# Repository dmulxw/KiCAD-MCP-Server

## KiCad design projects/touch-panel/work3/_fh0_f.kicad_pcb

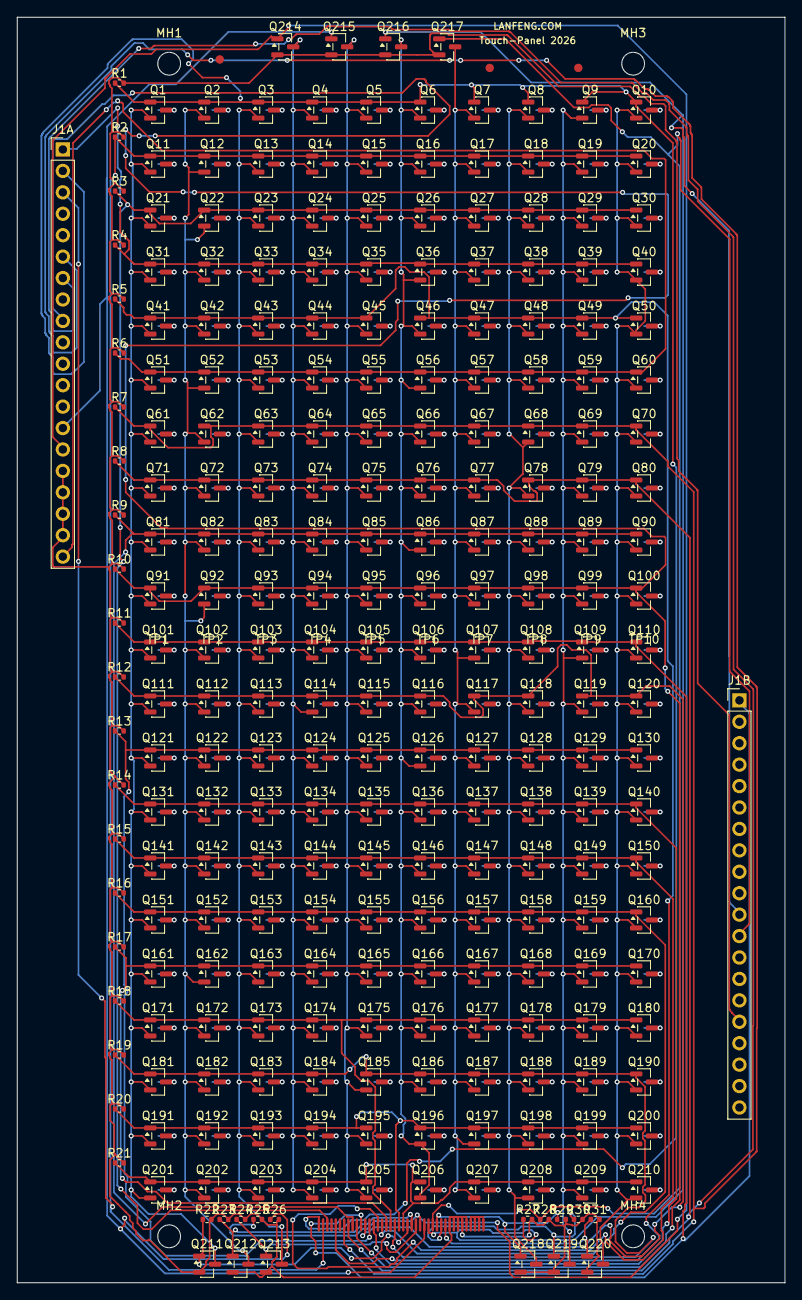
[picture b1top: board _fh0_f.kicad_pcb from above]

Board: 2 copper layers, 91.0 x 150.0 mm, 270 parts (0 on the bottom side), 253 nets.

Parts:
J1A, J1B: PinHeader_1x20_P2.54mm_Vertical
MH1, MH2, MH3, MH4: MountingHole_2.7mm
MK1, MK2, MK3: Fiducial_1mm_Mask2mm
Q1, Q2, Q3, Q4, Q5, Q6, Q7, Q8, Q9, Q10, Q11, Q12, Q13, Q14, Q15, Q16, Q17, Q18, Q19, Q20, Q21, Q22, Q23, Q24, Q25, Q26, Q27, Q28, Q29, Q30, Q31, Q32, Q33, Q34, Q35, Q36, Q37, Q38, Q39, Q40, Q41, Q42, Q43, Q44, Q45, Q46, Q47, Q48, Q49, Q50, Q51, Q52, Q53, Q54, Q55, Q56, Q57, Q58, Q59, Q60, Q61, Q62, Q63, Q64, Q65, Q66, Q67, Q68, Q69, Q70, Q71, Q72, Q73, Q74, Q75, Q76, Q77, Q78, Q79, Q80, Q81, Q82, Q83, Q84, Q85, Q86, Q87, Q88, Q89, Q90, Q91, Q92, Q93, Q94, Q95, Q96, Q97, Q98, Q99, Q100, Q101, Q102, Q103, Q104, Q105, Q106, Q107, Q108, Q109, Q110, Q111, Q112, Q113, Q114, Q115, Q116, Q117, Q118, Q119, Q120, Q121, Q122, Q123, Q124, Q125, Q126, Q127, Q128, Q129, Q130, Q131, Q132, Q133, Q134, Q135, Q136, Q137, Q138, Q139, Q140, Q141, Q142, Q143, Q144, Q145, Q146, Q147, Q148, Q149, Q150, Q151, Q152, Q153, Q154, Q155, Q156, Q157, Q158, Q159, Q160, Q161, Q162, Q163, Q164, Q165, Q166, Q167, Q168, Q169, Q170, Q171, Q172, Q173, Q174, Q175, Q176, Q177, Q178, Q179, Q180, Q181, Q182, Q183, Q184, Q185, Q186, Q187, Q188, Q189, Q190, Q191, Q192, Q193, Q194, Q195, Q196, Q197, Q198, Q199, Q200, Q201, Q202, Q203, Q204, Q205, Q206, Q207, Q208, Q209, Q210, Q211, Q212, Q213, Q214, Q215, Q216, Q217, Q218, Q219, Q220: AO3400; SOT-23
R1, R2, R3, R4, R5, R6, R7, R8, R9, R10, R11, R12, R13, R14, R15, R16, R17, R18, R19, R20, R21, R22, R23, R24, R25, R26, R27, R28, R29, R30, R31: 10k; R_0402_1005Metric
TP1, TP2, TP3, TP4, TP5, TP6, TP7, TP8, TP9, TP10: TouchPadColumn

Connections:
+3V3: J1B.17, J1B.18, J1B.19, J1B.20
COL0: Q1.2, Q11.2, Q21.2, Q31.2, Q41.2, Q51.2, Q61.2, Q71.2, Q81.2, Q91.2, Q101.2, Q111.2, Q121.2, Q131.2, Q141.2, Q151.2, Q161.2, Q171.2, Q181.2, Q191.2, Q201.2, Q211.3
COL1: Q2.2, Q12.2, Q22.2, Q32.2, Q42.2, Q52.2, Q62.2, Q72.2, Q82.2, Q92.2, Q102.2, Q112.2, Q122.2, Q132.2, Q142.2, Q152.2, Q162.2, Q172.2, Q182.2, Q192.2, Q202.2, Q212.3
COL2: Q3.2, Q13.2, Q23.2, Q33.2, Q43.2, Q53.2, Q63.2, Q73.2, Q83.2, Q93.2, Q103.2, Q113.2, Q123.2, Q133.2, Q143.2, Q153.2, Q163.2, Q173.2, Q183.2, Q193.2, Q203.2, Q213.3
COL3: Q4.2, Q14.2, Q24.2, Q34.2, Q44.2, Q54.2, Q64.2, Q74.2, Q84.2, Q94.2, Q104.2, Q114.2, Q124.2, Q134.2, Q144.2, Q154.2, Q164.2, Q174.2, Q184.2, Q194.2, Q204.2, Q214.3
COL4: Q5.2, Q15.2, Q25.2, Q35.2, Q45.2, Q55.2, Q65.2, Q75.2, Q85.2, Q95.2, Q105.2, Q115.2, Q125.2, Q135.2, Q145.2, Q155.2, Q165.2, Q175.2, Q185.2, Q195.2, Q205.2, Q215.3
COL5: Q6.2, Q16.2, Q26.2, Q36.2, Q46.2, Q56.2, Q66.2, Q76.2, Q86.2, Q96.2, Q106.2, Q116.2, Q126.2, Q136.2, Q146.2, Q156.2, Q166.2, Q176.2, Q186.2, Q196.2, Q206.2, Q216.3
COL6: Q7.2, Q17.2, Q27.2, Q37.2, Q47.2, Q57.2, Q67.2, Q77.2, Q87.2, Q97.2, Q107.2, Q117.2, Q127.2, Q137.2, Q147.2, Q157.2, Q167.2, Q177.2, Q187.2, Q197.2, Q207.2, Q217.3
COL7: Q8.2, Q18.2, Q28.2, Q38.2, Q48.2, Q58.2, Q68.2, Q78.2, Q88.2, Q98.2, Q108.2, Q118.2, Q128.2, Q138.2, Q148.2, Q158.2, Q168.2, Q178.2, Q188.2, Q198.2, Q208.2, Q218.3
COL8: Q9.2, Q19.2, Q29.2, Q39.2, Q49.2, Q59.2, Q69.2, Q79.2, Q89.2, Q99.2, Q109.2, Q119.2, Q129.2, Q139.2, Q149.2, Q159.2, Q169.2, Q179.2, Q189.2, Q199.2, Q209.2, Q219.3
COL9: Q10.2, Q20.2, Q30.2, Q40.2, Q50.2, Q60.2, Q70.2, Q80.2, Q90.2, Q100.2, Q110.2, Q120.2, Q130.2, Q140.2, Q150.2, Q160.2, Q170.2, Q180.2, Q190.2, Q200.2, Q210.2, Q220.3
CSEL0: J1B.8, Q211.1, R22.1
CSEL1: J1B.9, Q212.1, R23.1
CSEL2: J1B.10, Q213.1, R24.1
CSEL3: J1A.15, Q214.1, R25.1
CSEL4: J1A.14, Q215.1, R26.1
CSEL5: J1B.11, Q216.1, R27.1
CSEL6: J1B.12, Q217.1, R28.1
CSEL7: J1B.13, Q218.1, R29.1
CSEL8: J1B.14, Q219.1, R30.1
CSEL9: J1B.15, Q220.1, R31.1
GND: J1A.16, J1A.17, J1A.18, J1A.19, J1B.16, Q211.2, Q212.2, Q213.2, Q214.2, Q215.2, Q216.2, Q217.2, Q218.2, Q219.2, Q220.2, R1.2, R2.2, R3.2, R4.2, R5.2, R6.2, R7.2, R8.2, R9.2, R10.2, R11.2, R12.2, R13.2, R14.2, R15.2, R16.2, R17.2, R18.2, R19.2, R20.2, R21.2, R22.2, R23.2, R24.2, R25.2, R26.2, R27.2, R28.2, R29.2, R30.2, R31.2
PAD1: Q1.3, TP1.1
PAD2: Q2.3, TP2.1
PAD3: Q3.3, TP3.1
PAD4: Q4.3, TP4.1
PAD5: Q5.3, TP5.1
PAD6: Q6.3, TP6.1
PAD7: Q7.3, TP7.1
PAD8: Q8.3, TP8.1
PAD9: Q9.3, TP9.1
PAD10: Q10.3, TP10.1
PAD11: Q11.3, TP1.2
PAD12: Q12.3, TP2.2
PAD13: Q13.3, TP3.2
PAD14: Q14.3, TP4.2
PAD15: Q15.3, TP5.2
PAD16: Q16.3, TP6.2
PAD17: Q17.3, TP7.2
PAD18: Q18.3, TP8.2
PAD19: Q19.3, TP9.2
PAD20: Q20.3, TP10.2
PAD21: Q21.3, TP1.3
PAD22: Q22.3, TP2.3
PAD23: Q23.3, TP3.3
PAD24: Q24.3, TP4.3
PAD25: Q25.3, TP5.3
PAD26: Q26.3, TP6.3
PAD27: Q27.3, TP7.3
PAD28: Q28.3, TP8.3
PAD29: Q29.3, TP9.3
PAD30: Q30.3, TP10.3
PAD31: Q31.3, TP1.4
PAD32: Q32.3, TP2.4
PAD33: Q33.3, TP3.4
PAD34: Q34.3, TP4.4
PAD35: Q35.3, TP5.4
PAD36: Q36.3, TP6.4
PAD37: Q37.3, TP7.4
PAD38: Q38.3, TP8.4
PAD39: Q39.3, TP9.4
PAD40: Q40.3, TP10.4
PAD41: Q41.3, TP1.5
PAD42: Q42.3, TP2.5
PAD43: Q43.3, TP3.5
PAD44: Q44.3, TP4.5
PAD45: Q45.3, TP5.5
PAD46: Q46.3, TP6.5
PAD47: Q47.3, TP7.5
PAD48: Q48.3, TP8.5
PAD49: Q49.3, TP9.5
PAD50: Q50.3, TP10.5
PAD51: Q51.3, TP1.6
PAD52: Q52.3, TP2.6
PAD53: Q53.3, TP3.6
PAD54: Q54.3, TP4.6
PAD55: Q55.3, TP5.6
PAD56: Q56.3, TP6.6
PAD57: Q57.3, TP7.6
PAD58: Q58.3, TP8.6
PAD59: Q59.3, TP9.6
PAD60: Q60.3, TP10.6
PAD61: Q61.3, TP1.7
PAD62: Q62.3, TP2.7
PAD63: Q63.3, TP3.7
PAD64: Q64.3, TP4.7
PAD65: Q65.3, TP5.7
PAD66: Q66.3, TP6.7
PAD67: Q67.3, TP7.7
PAD68: Q68.3, TP8.7
PAD69: Q69.3, TP9.7
PAD70: Q70.3, TP10.7
PAD71: Q71.3, TP1.8
PAD72: Q72.3, TP2.8
PAD73: Q73.3, TP3.8
PAD74: Q74.3, TP4.8
PAD75: Q75.3, TP5.8
PAD76: Q76.3, TP6.8
PAD77: Q77.3, TP7.8
PAD78: Q78.3, TP8.8
PAD79: Q79.3, TP9.8
PAD80: Q80.3, TP10.8
PAD81: Q81.3, TP1.9
PAD82: Q82.3, TP2.9
PAD83: Q83.3, TP3.9
PAD84: Q84.3, TP4.9
PAD85: Q85.3, TP5.9
PAD86: Q86.3, TP6.9
PAD87: Q87.3, TP7.9
PAD88: Q88.3, TP8.9
PAD89: Q89.3, TP9.9
PAD90: Q90.3, TP10.9
PAD91: Q91.3, TP1.10
PAD92: Q92.3, TP2.10
PAD93: Q93.3, TP3.10
PAD94: Q94.3, TP4.10
PAD95: Q95.3, TP5.10
PAD96: Q96.3, TP6.10
PAD97: Q97.3, TP7.10
PAD98: Q98.3, TP8.10
PAD99: Q99.3, TP9.10
PAD100: Q100.3, TP10.10
PAD101: Q101.3, TP1.11
PAD102: Q102.3, TP2.11
PAD103: Q103.3, TP3.11
PAD104: Q104.3, TP4.11
PAD105: Q105.3, TP5.11
PAD106: Q106.3, TP6.11
PAD107: Q107.3, TP7.11
PAD108: Q108.3, TP8.11
PAD109: Q109.3, TP9.11
PAD110: Q110.3, TP10.11
PAD111: Q111.3, TP1.12
PAD112: Q112.3, TP2.12
PAD113: Q113.3, TP3.12
PAD114: Q114.3, TP4.12
PAD115: Q115.3, TP5.12
PAD116: Q116.3, TP6.12
PAD117: Q117.3, TP7.12
PAD118: Q118.3, TP8.12
PAD119: Q119.3, TP9.12
PAD120: Q120.3, TP10.12
PAD121: Q121.3, TP1.13
PAD122: Q122.3, TP2.13
PAD123: Q123.3, TP3.13
PAD124: Q124.3, TP4.13
PAD125: Q125.3, TP5.13
PAD126: Q126.3, TP6.13
PAD127: Q127.3, TP7.13
PAD128: Q128.3, TP8.13
PAD129: Q129.3, TP9.13
PAD130: Q130.3, TP10.13
PAD131: Q131.3, TP1.14
PAD132: Q132.3, TP2.14
PAD133: Q133.3, TP3.14
PAD134: Q134.3, TP4.14
PAD135: Q135.3, TP5.14
PAD136: Q136.3, TP6.14
PAD137: Q137.3, TP7.14
PAD138: Q138.3, TP8.14
PAD139: Q139.3, TP9.14
PAD140: Q140.3, TP10.14
PAD141: Q141.3, TP1.15
PAD142: Q142.3, TP2.15
PAD143: Q143.3, TP3.15
PAD144: Q144.3, TP4.15
PAD145: Q145.3, TP5.15
PAD146: Q146.3, TP6.15
PAD147: Q147.3, TP7.15
PAD148: Q148.3, TP8.15
PAD149: Q149.3, TP9.15
PAD150: Q150.3, TP10.15
PAD151: Q151.3, TP1.16
PAD152: Q152.3, TP2.16
PAD153: Q153.3, TP3.16
PAD154: Q154.3, TP4.16
PAD155: Q155.3, TP5.16
PAD156: Q156.3, TP6.16
PAD157: Q157.3, TP7.16
PAD158: Q158.3, TP8.16
PAD159: Q159.3, TP9.16
PAD160: Q160.3, TP10.16
PAD161: Q161.3, TP1.17
PAD162: Q162.3, TP2.17
PAD163: Q163.3, TP3.17
PAD164: Q164.3, TP4.17
PAD165: Q165.3, TP5.17
PAD166: Q166.3, TP6.17
PAD167: Q167.3, TP7.17
PAD168: Q168.3, TP8.17
PAD169: Q169.3, TP9.17
PAD170: Q170.3, TP10.17
PAD171: Q171.3, TP1.18
PAD172: Q172.3, TP2.18
PAD173: Q173.3, TP3.18
PAD174: Q174.3, TP4.18
PAD175: Q175.3, TP5.18
PAD176: Q176.3, TP6.18
PAD177: Q177.3, TP7.18
PAD178: Q178.3, TP8.18
PAD179: Q179.3, TP9.18
PAD180: Q180.3, TP10.18
PAD181: Q181.3, TP1.19
PAD182: Q182.3, TP2.19
PAD183: Q183.3, TP3.19
PAD184: Q184.3, TP4.19
PAD185: Q185.3, TP5.19
PAD186: Q186.3, TP6.19
PAD187: Q187.3, TP7.19
PAD188: Q188.3, TP8.19
PAD189: Q189.3, TP9.19
PAD190: Q190.3, TP10.19
PAD191: Q191.3, TP1.20
PAD192: Q192.3, TP2.20
PAD193: Q193.3, TP3.20
PAD194: Q194.3, TP4.20
PAD195: Q195.3, TP5.20
PAD196: Q196.3, TP6.20
PAD197: Q197.3, TP7.20
PAD198: Q198.3, TP8.20
PAD199: Q199.3, TP9.20
PAD200: Q200.3, TP10.20
PAD201: Q201.3, TP1.21
PAD202: Q202.3, TP2.21
PAD203: Q203.3, TP3.21
PAD204: Q204.3, TP4.21
PAD205: Q205.3, TP5.21
PAD206: Q206.3, TP6.21
PAD207: Q207.3, TP7.21
PAD208: Q208.3, TP8.21
PAD209: Q209.3, TP9.21
PAD210: Q210.3, TP10.21
ROW0: J1A.2, Q1.1, Q2.1, Q3.1, Q4.1, Q5.1, Q6.1, Q7.1, Q8.1, Q9.1, Q10.1, R1.1
ROW1: J1A.3, Q11.1, Q12.1, Q13.1, Q14.1, Q15.1, Q16.1, Q17.1, Q18.1, Q19.1, Q20.1, R2.1
ROW2: J1A.4, Q21.1, Q22.1, Q23.1, Q24.1, Q25.1, Q26.1, Q27.1, Q28.1, Q29.1, Q30.1, R3.1
ROW3: J1A.1, Q31.1, Q32.1, Q33.1, Q34.1, Q35.1, Q36.1, Q37.1, Q38.1, Q39.1, Q40.1, R4.1
ROW4: J1A.5, Q41.1, Q42.1, Q43.1, Q44.1, Q45.1, Q46.1, Q47.1, Q48.1, Q49.1, Q50.1, R5.1
ROW5: J1A.20, Q51.1, Q52.1, Q53.1, Q54.1, Q55.1, Q56.1, Q57.1, Q58.1, Q59.1, Q60.1, R6.1
ROW6: J1A.6, Q61.1, Q62.1, Q63.1, Q64.1, Q65.1, Q66.1, Q67.1, Q68.1, Q69.1, Q70.1, R7.1
ROW7: J1A.7, Q71.1, Q72.1, Q73.1, Q74.1, Q75.1, Q76.1, Q77.1, Q78.1, Q79.1, Q80.1, R8.1
ROW8: J1A.8, Q81.1, Q82.1, Q83.1, Q84.1, Q85.1, Q86.1, Q87.1, Q88.1, Q89.1, Q90.1, R9.1
ROW9: J1A.9, Q91.1, Q92.1, Q93.1, Q94.1, Q95.1, Q96.1, Q97.1, Q98.1, Q99.1, Q100.1, R10.1
ROW10: J1B.1, Q101.1, Q102.1, Q103.1, Q104.1, Q105.1, Q106.1, Q107.1, Q108.1, Q109.1, Q110.1, R11.1
ROW11: J1B.2, Q111.1, Q112.1, Q113.1, Q114.1, Q115.1, Q116.1, Q117.1, Q118.1, Q119.1, Q120.1, R12.1
ROW12: J1B.3, Q121.1, Q122.1, Q123.1, Q124.1, Q125.1, Q126.1, Q127.1, Q128.1, Q129.1, Q130.1, R13.1
ROW13: J1A.10, Q131.1, Q132.1, Q133.1, Q134.1, Q135.1, Q136.1, Q137.1, Q138.1, Q139.1, Q140.1, R14.1
ROW14: J1A.11, Q141.1, Q142.1, Q143.1, Q144.1, Q145.1, Q146.1, Q147.1, Q148.1, Q149.1, Q150.1, R15.1
ROW15: J1B.4, Q151.1, Q152.1, Q153.1, Q154.1, Q155.1, Q156.1, Q157.1, Q158.1, Q159.1, Q160.1, R16.1
ROW16: J1A.12, Q161.1, Q162.1, Q163.1, Q164.1, Q165.1, Q166.1, Q167.1, Q168.1, Q169.1, Q170.1, R17.1
ROW17: J1A.13, Q171.1, Q172.1, Q173.1, Q174.1, Q175.1, Q176.1, Q177.1, Q178.1, Q179.1, Q180.1, R18.1
ROW18: J1B.5, Q181.1, Q182.1, Q183.1, Q184.1, Q185.1, Q186.1, Q187.1, Q188.1, Q189.1, Q190.1, R19.1
ROW19: J1B.6, Q191.1, Q192.1, Q193.1, Q194.1, Q195.1, Q196.1, Q197.1, Q198.1, Q199.1, Q200.1, R20.1
ROW20: J1B.7, Q201.1, Q202.1, Q203.1, Q204.1, Q205.1, Q206.1, Q207.1, Q208.1, Q209.1, Q210.1, R21.1
